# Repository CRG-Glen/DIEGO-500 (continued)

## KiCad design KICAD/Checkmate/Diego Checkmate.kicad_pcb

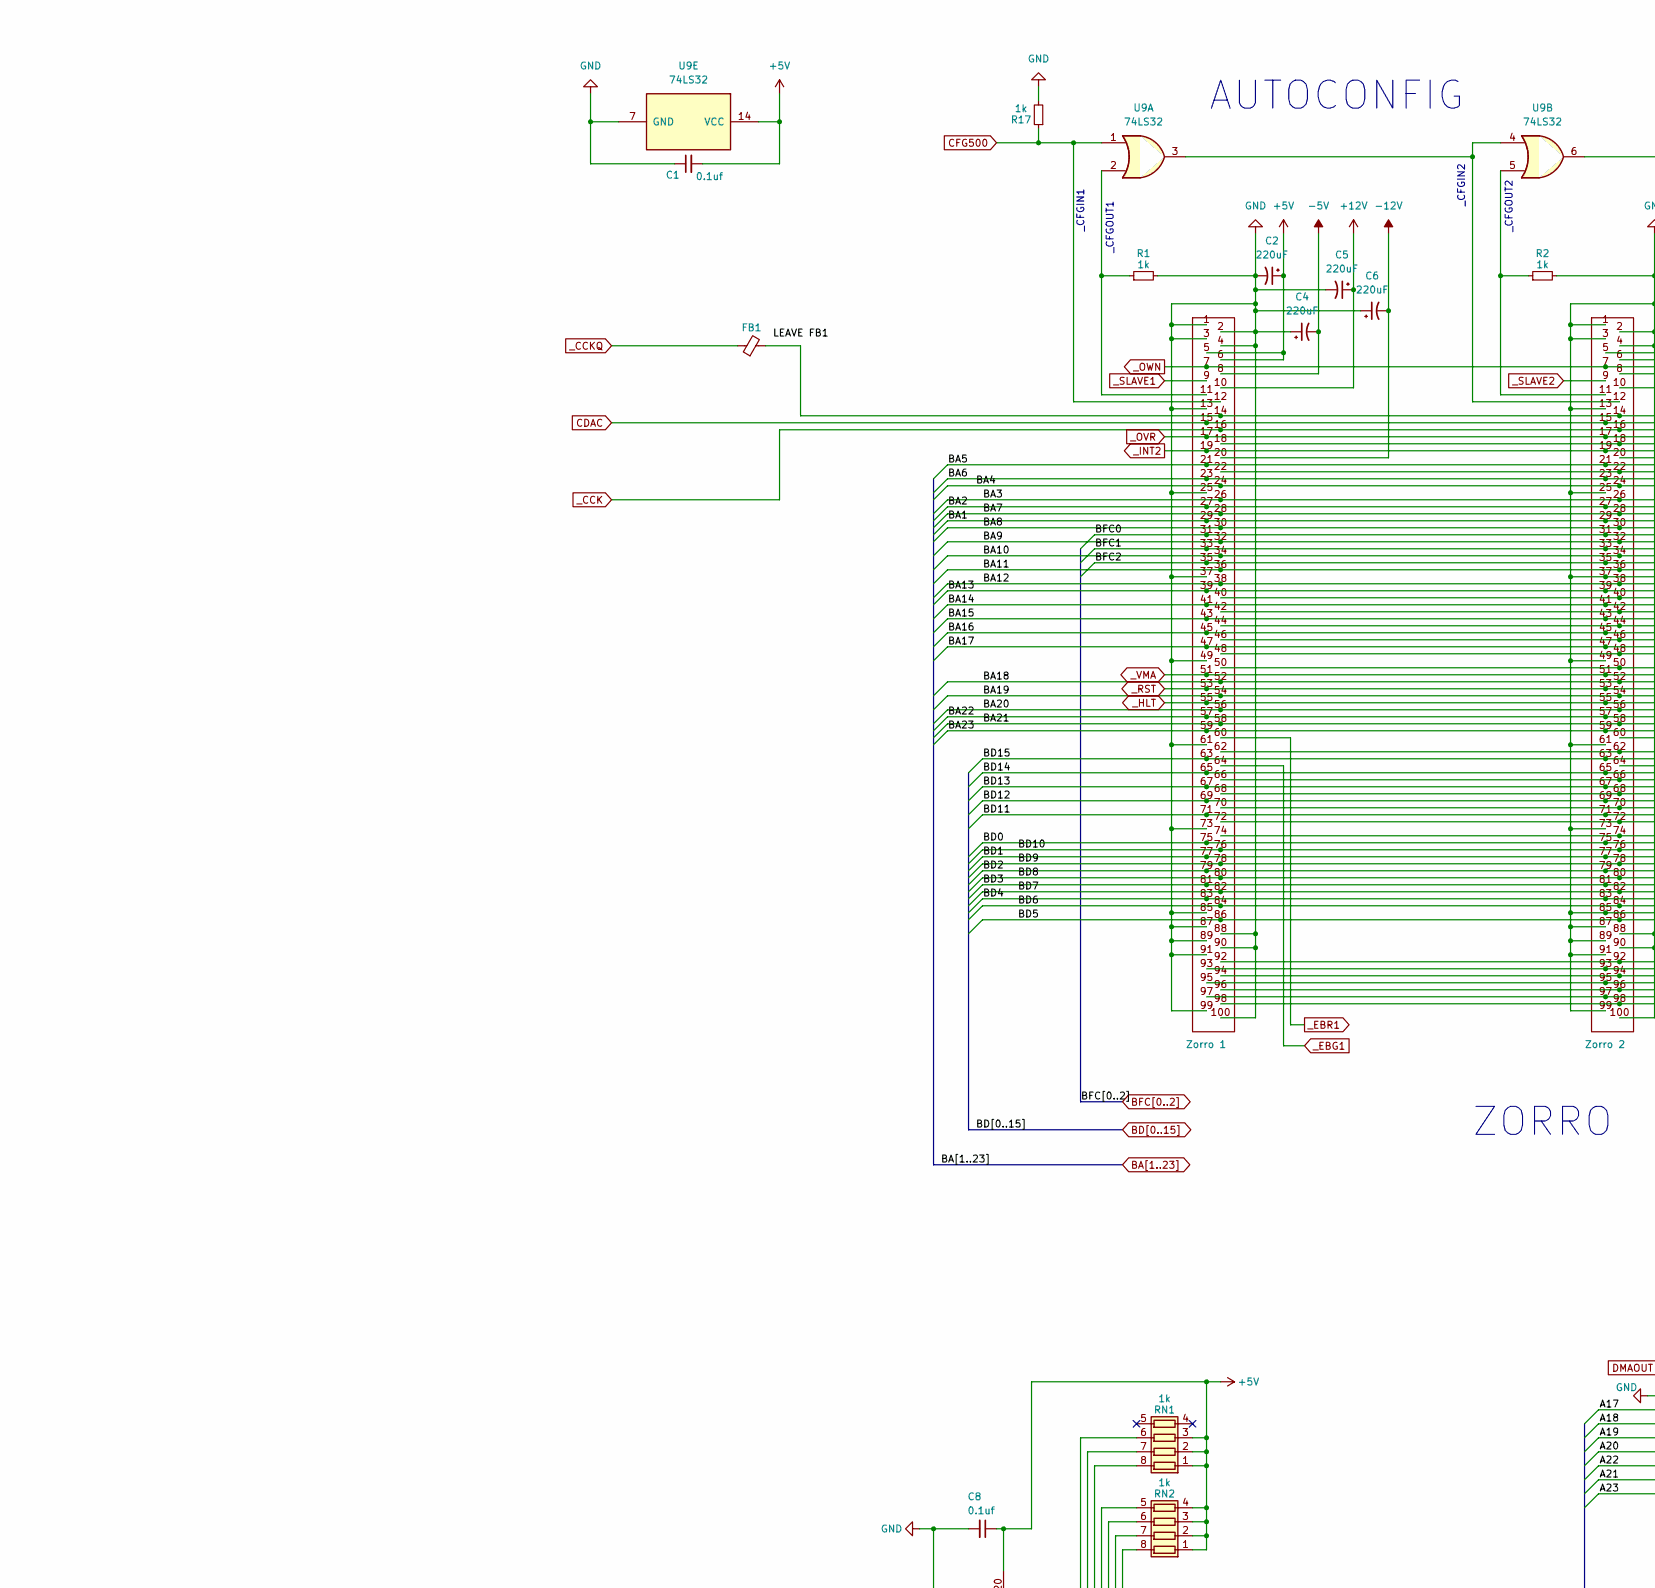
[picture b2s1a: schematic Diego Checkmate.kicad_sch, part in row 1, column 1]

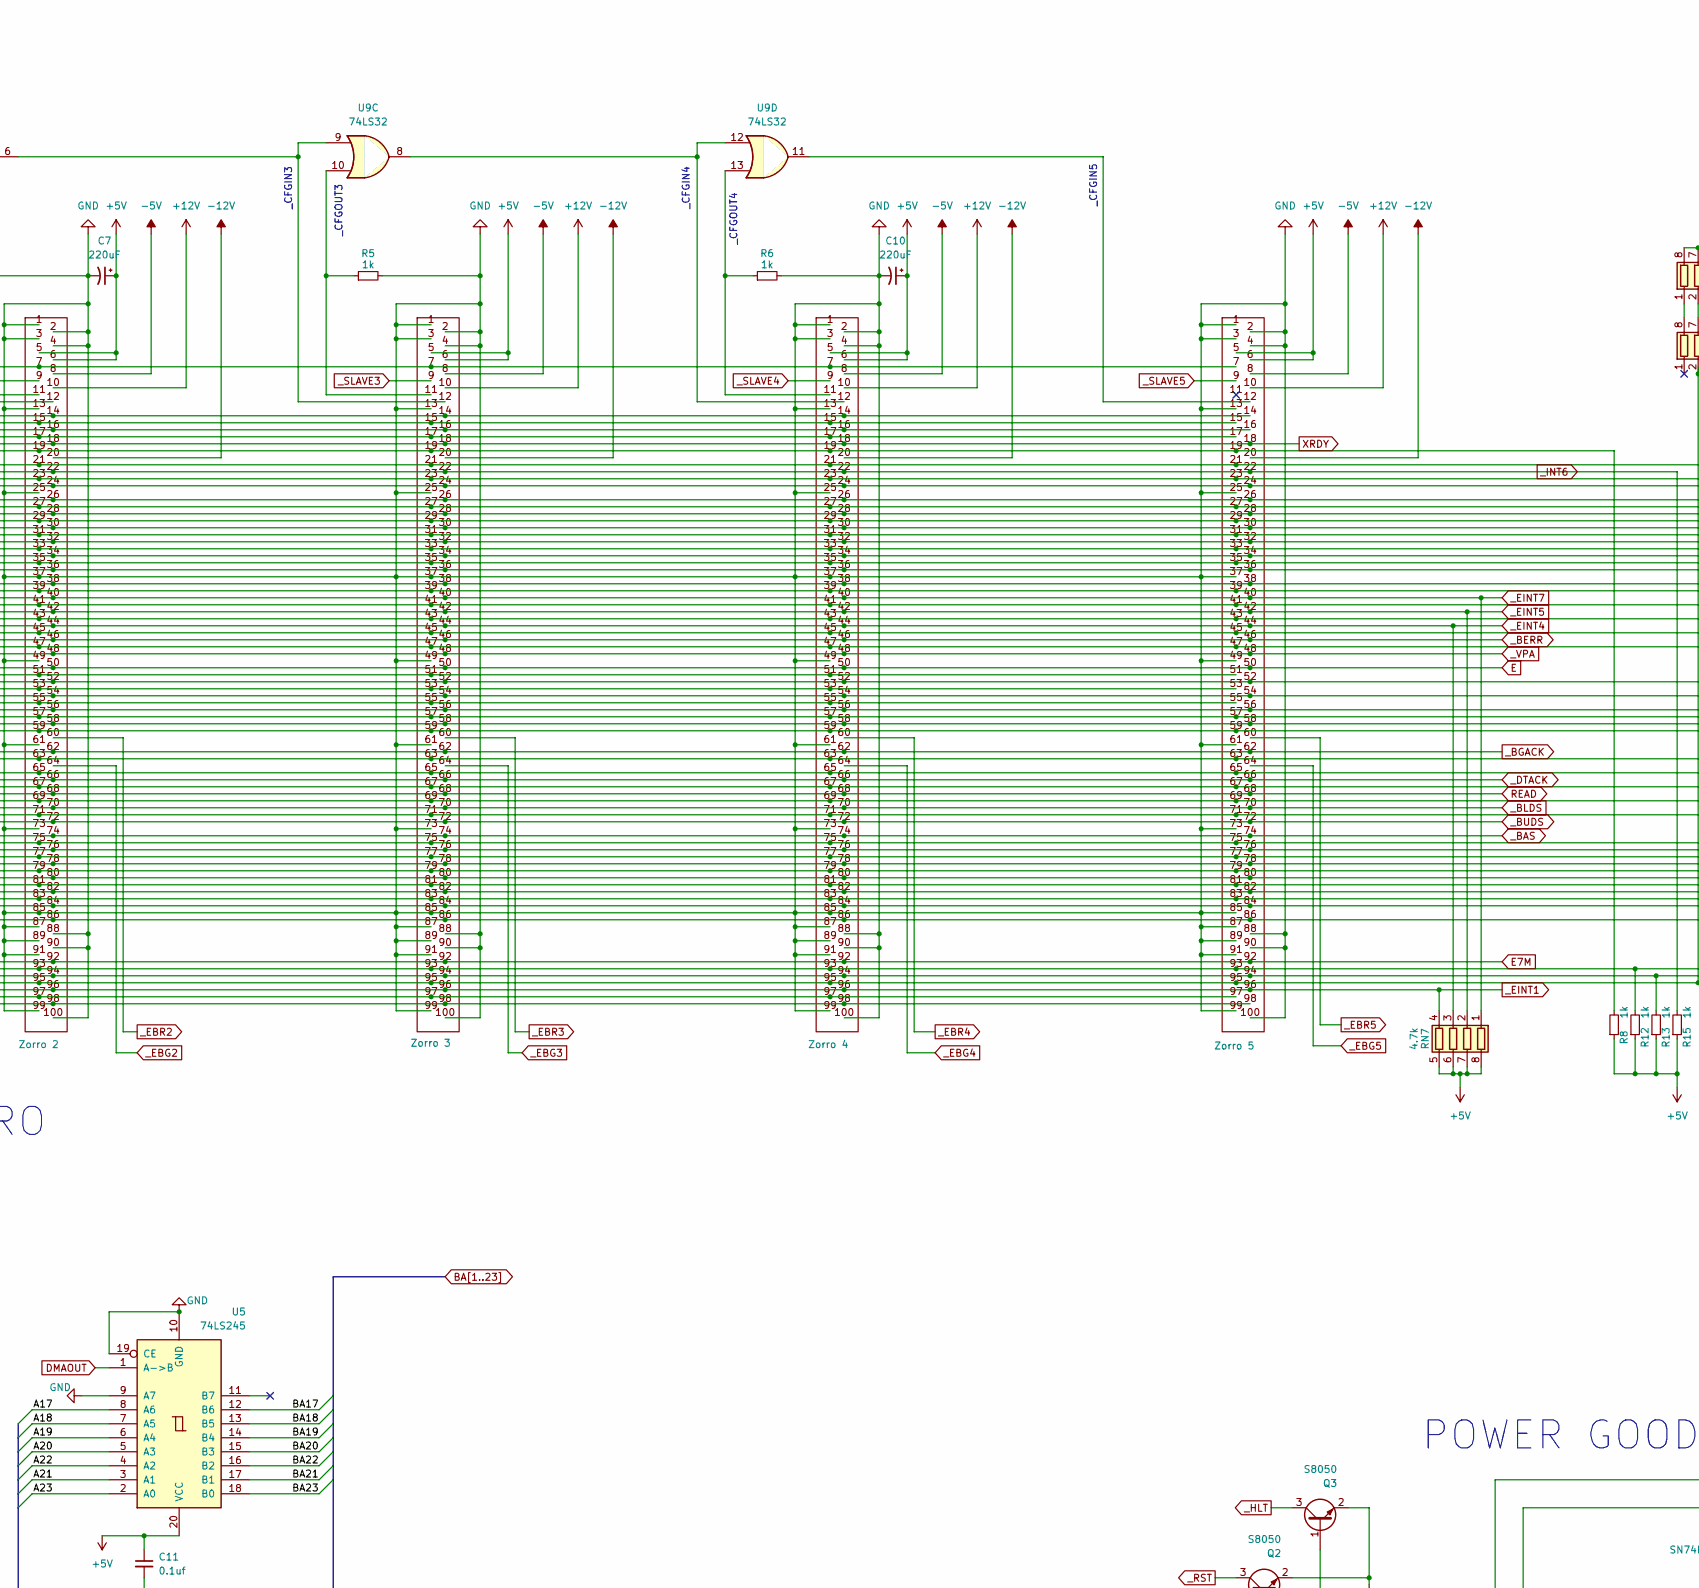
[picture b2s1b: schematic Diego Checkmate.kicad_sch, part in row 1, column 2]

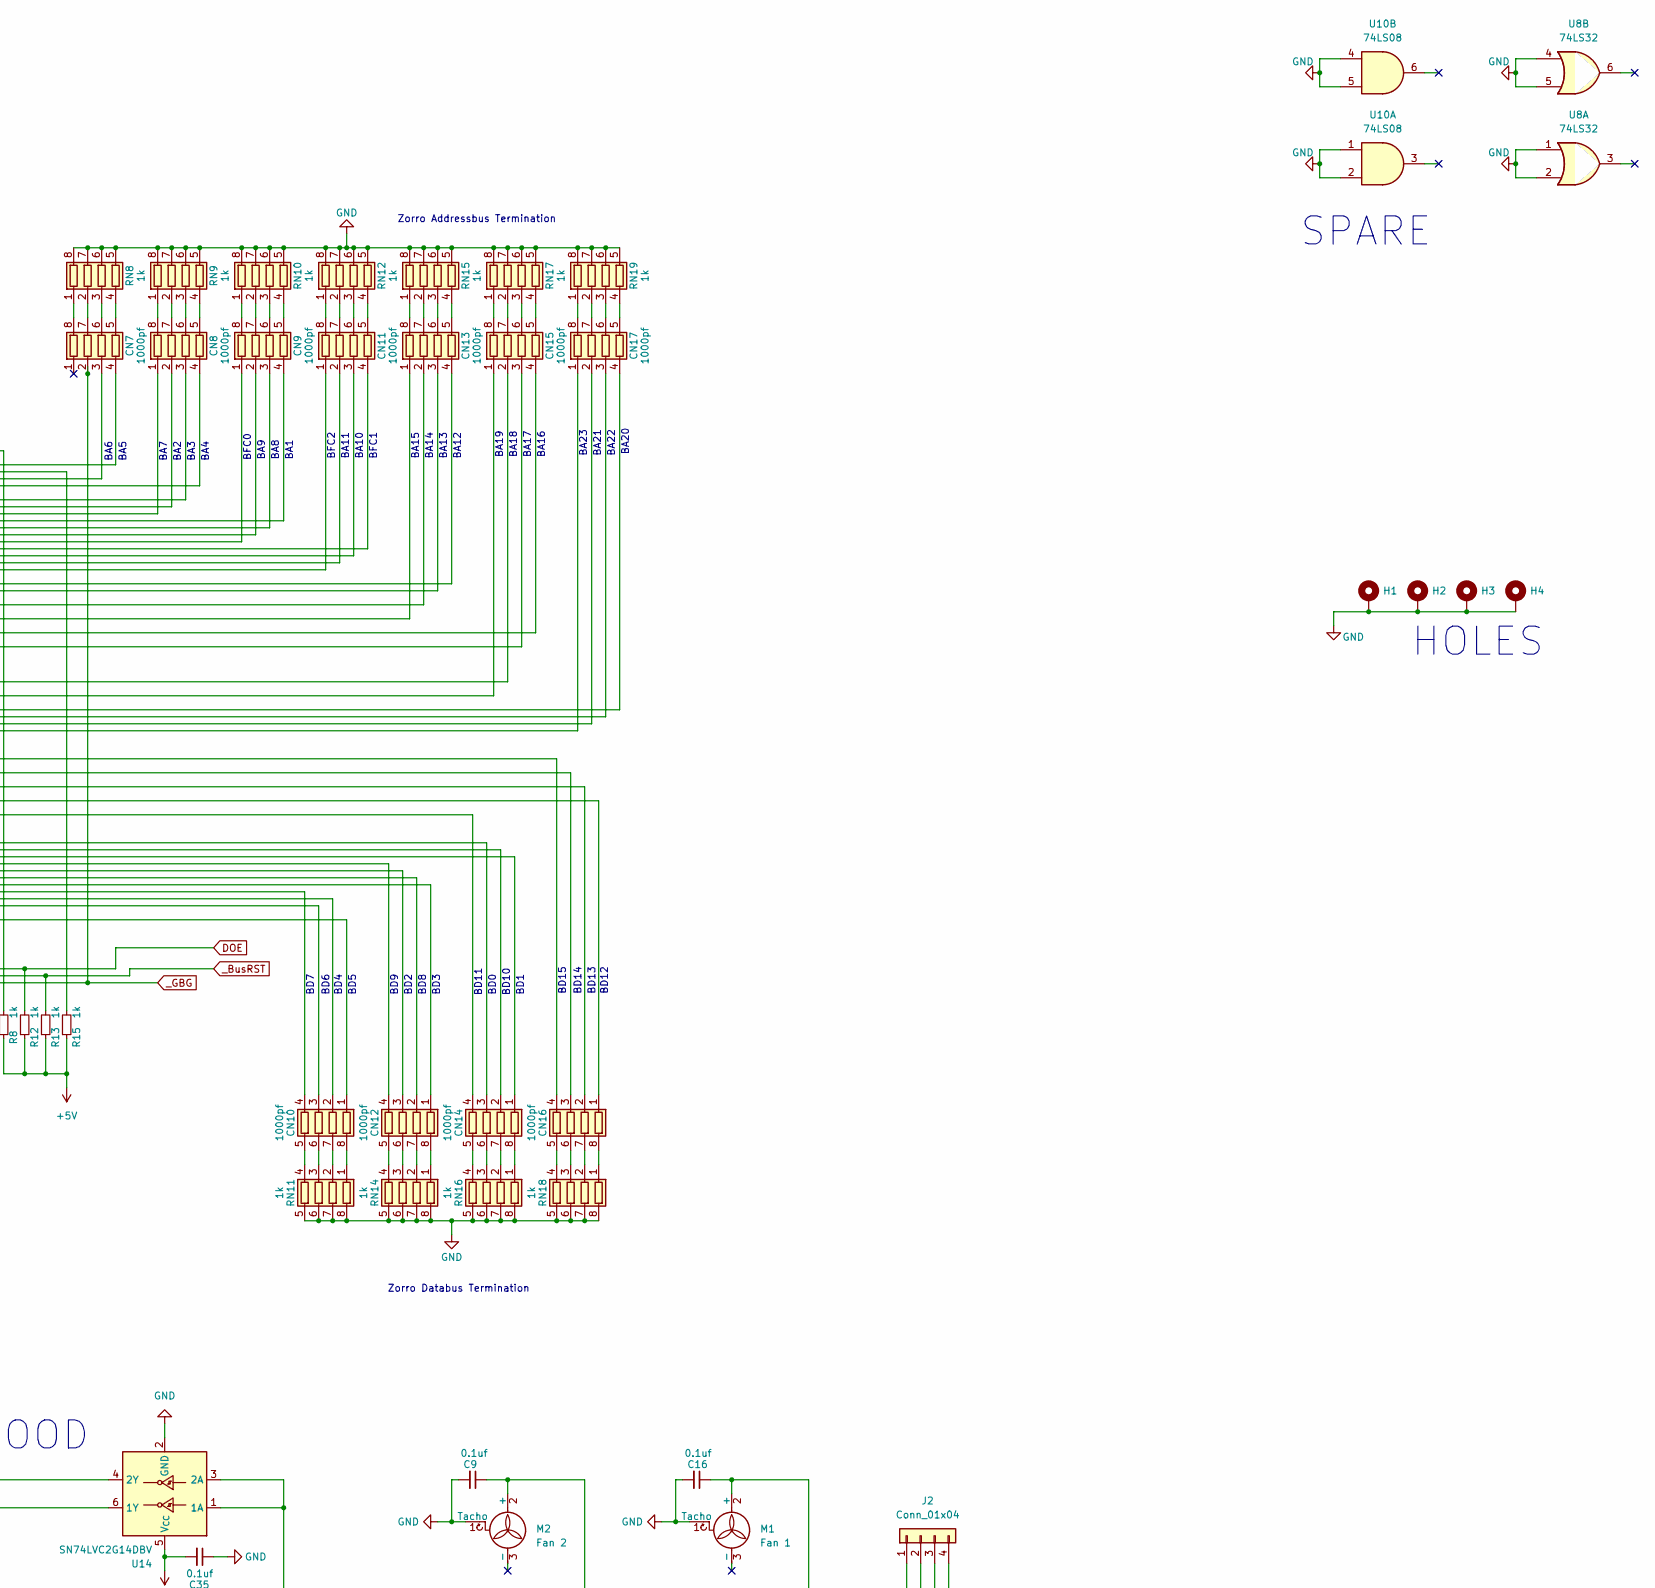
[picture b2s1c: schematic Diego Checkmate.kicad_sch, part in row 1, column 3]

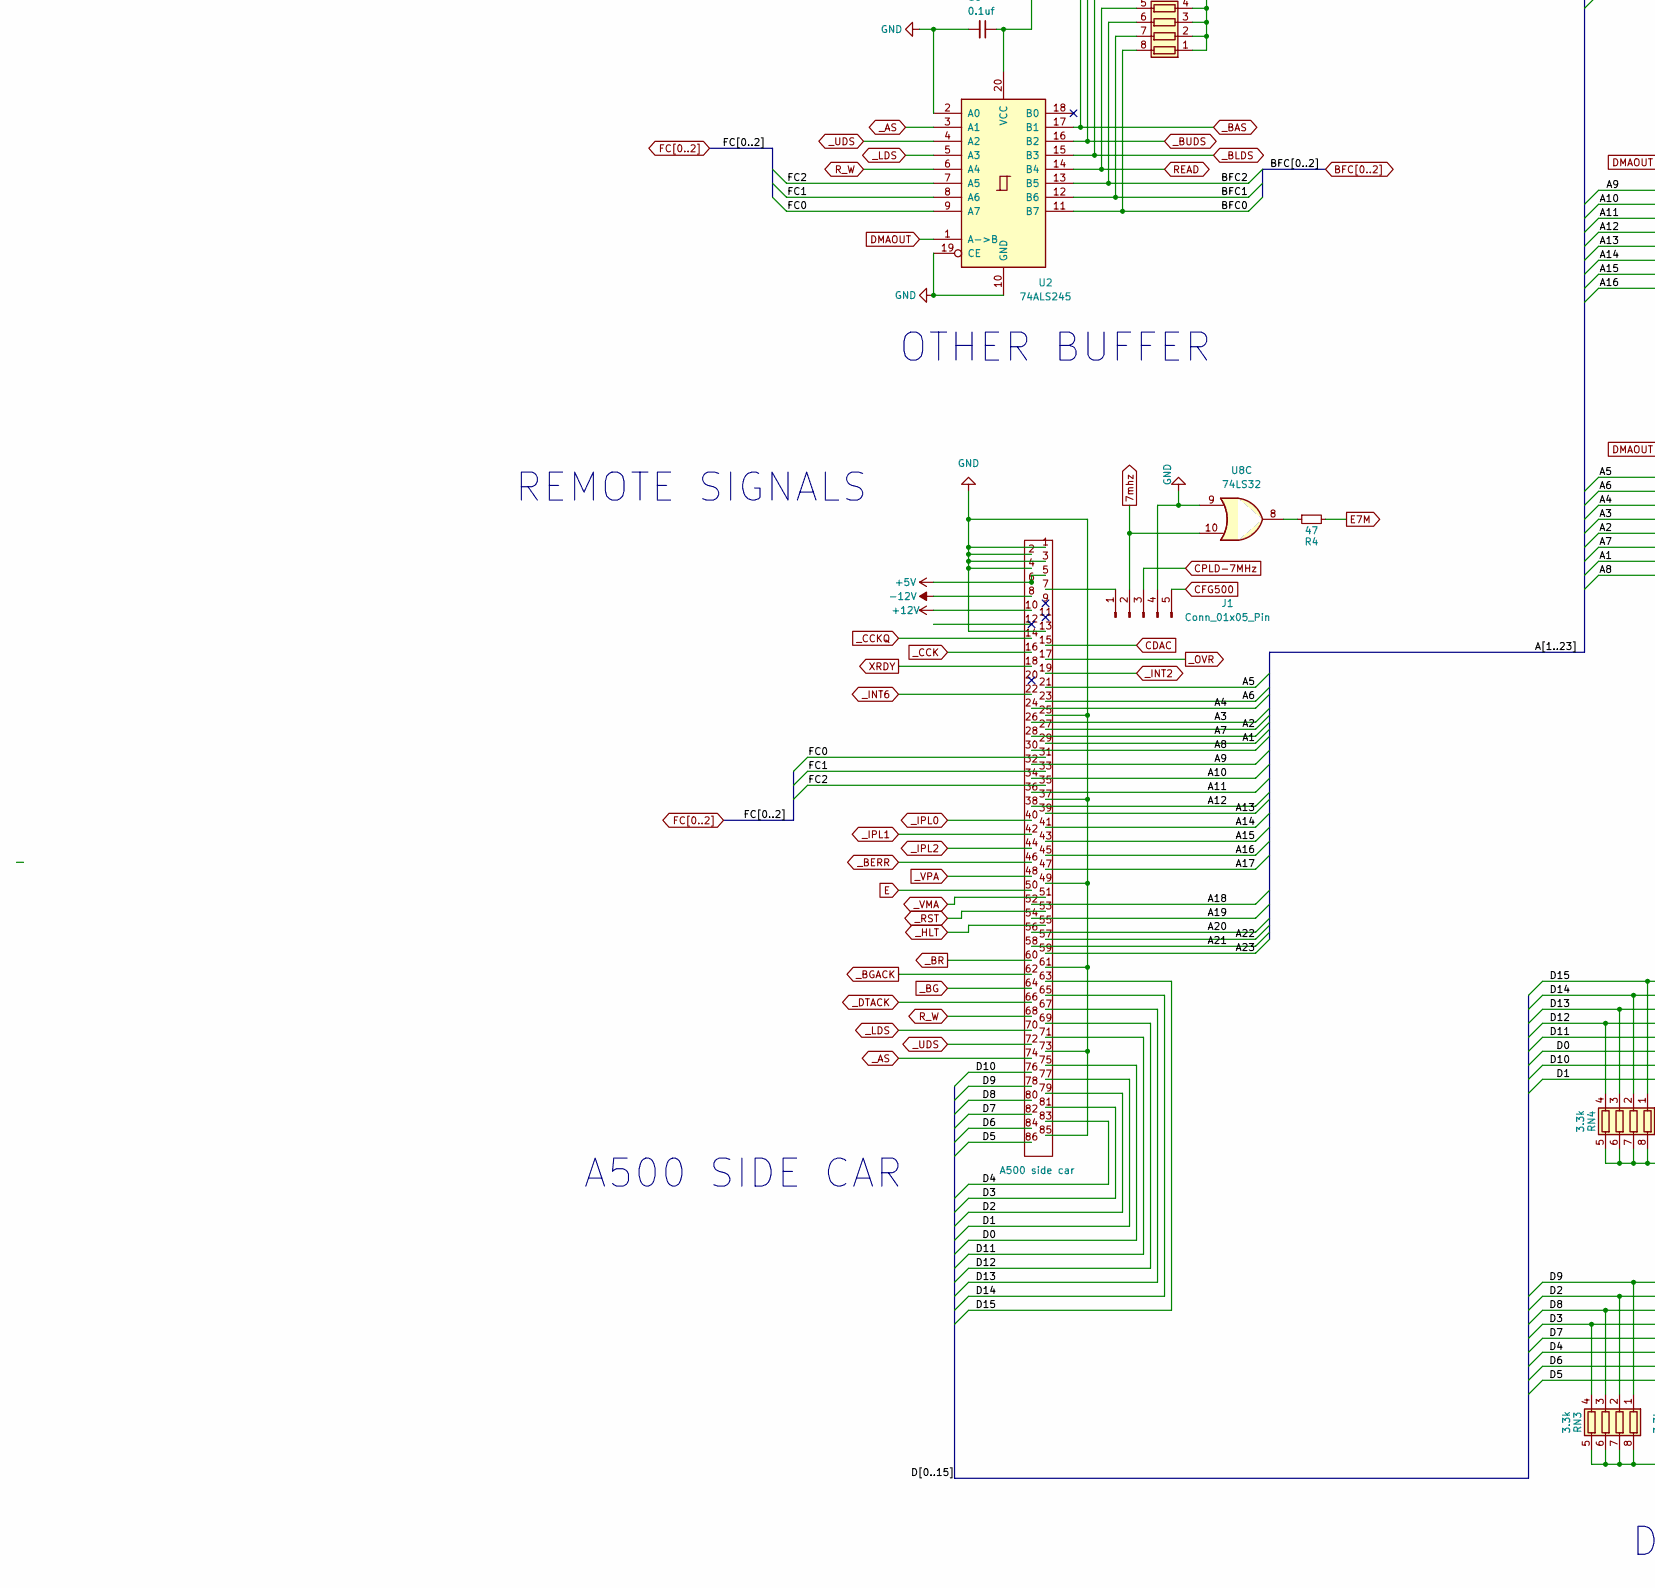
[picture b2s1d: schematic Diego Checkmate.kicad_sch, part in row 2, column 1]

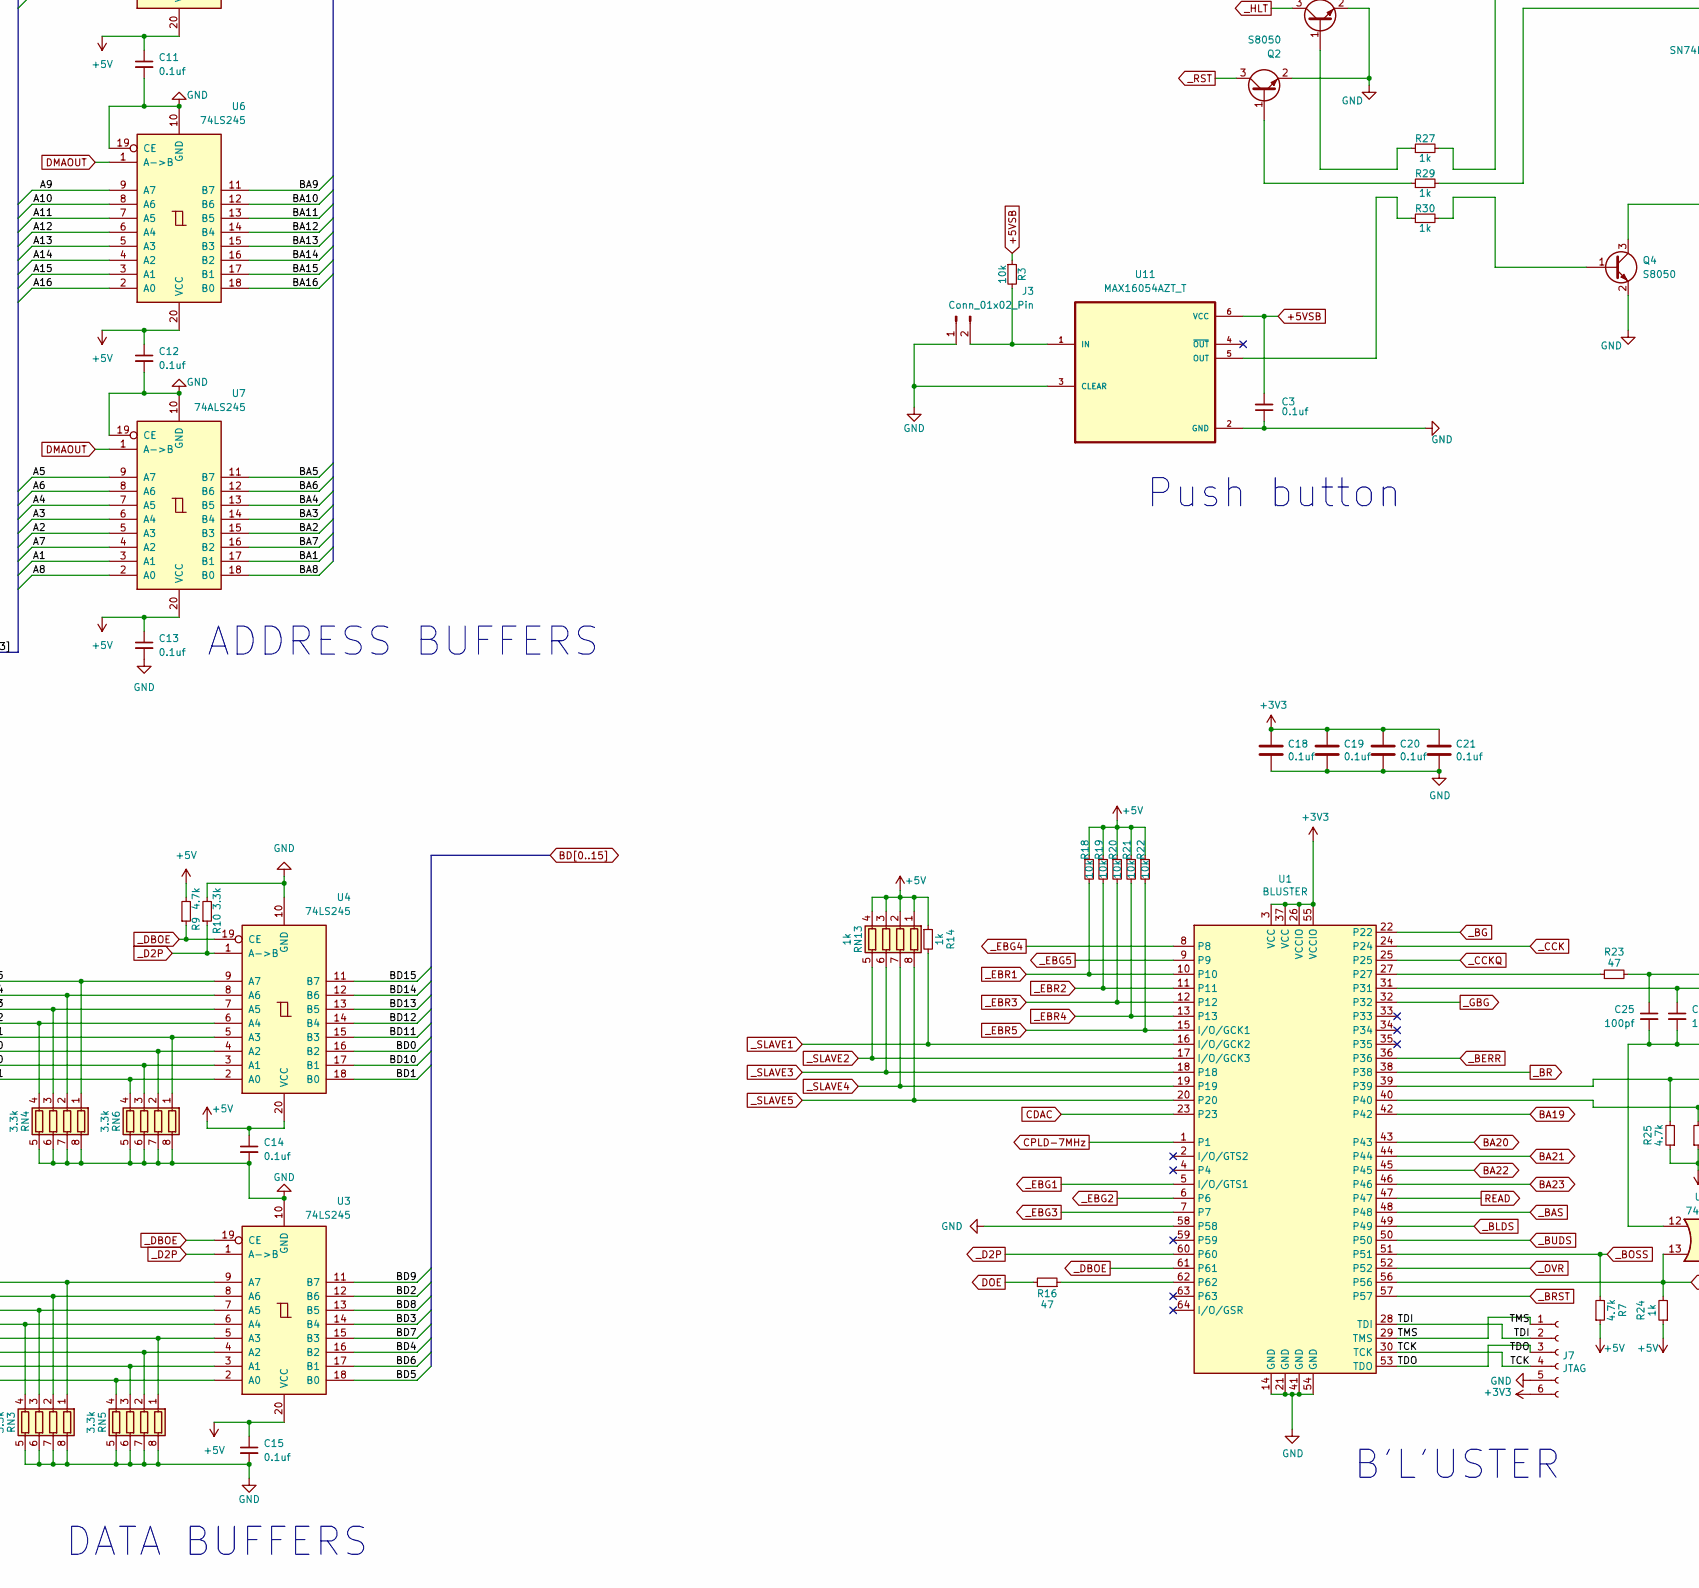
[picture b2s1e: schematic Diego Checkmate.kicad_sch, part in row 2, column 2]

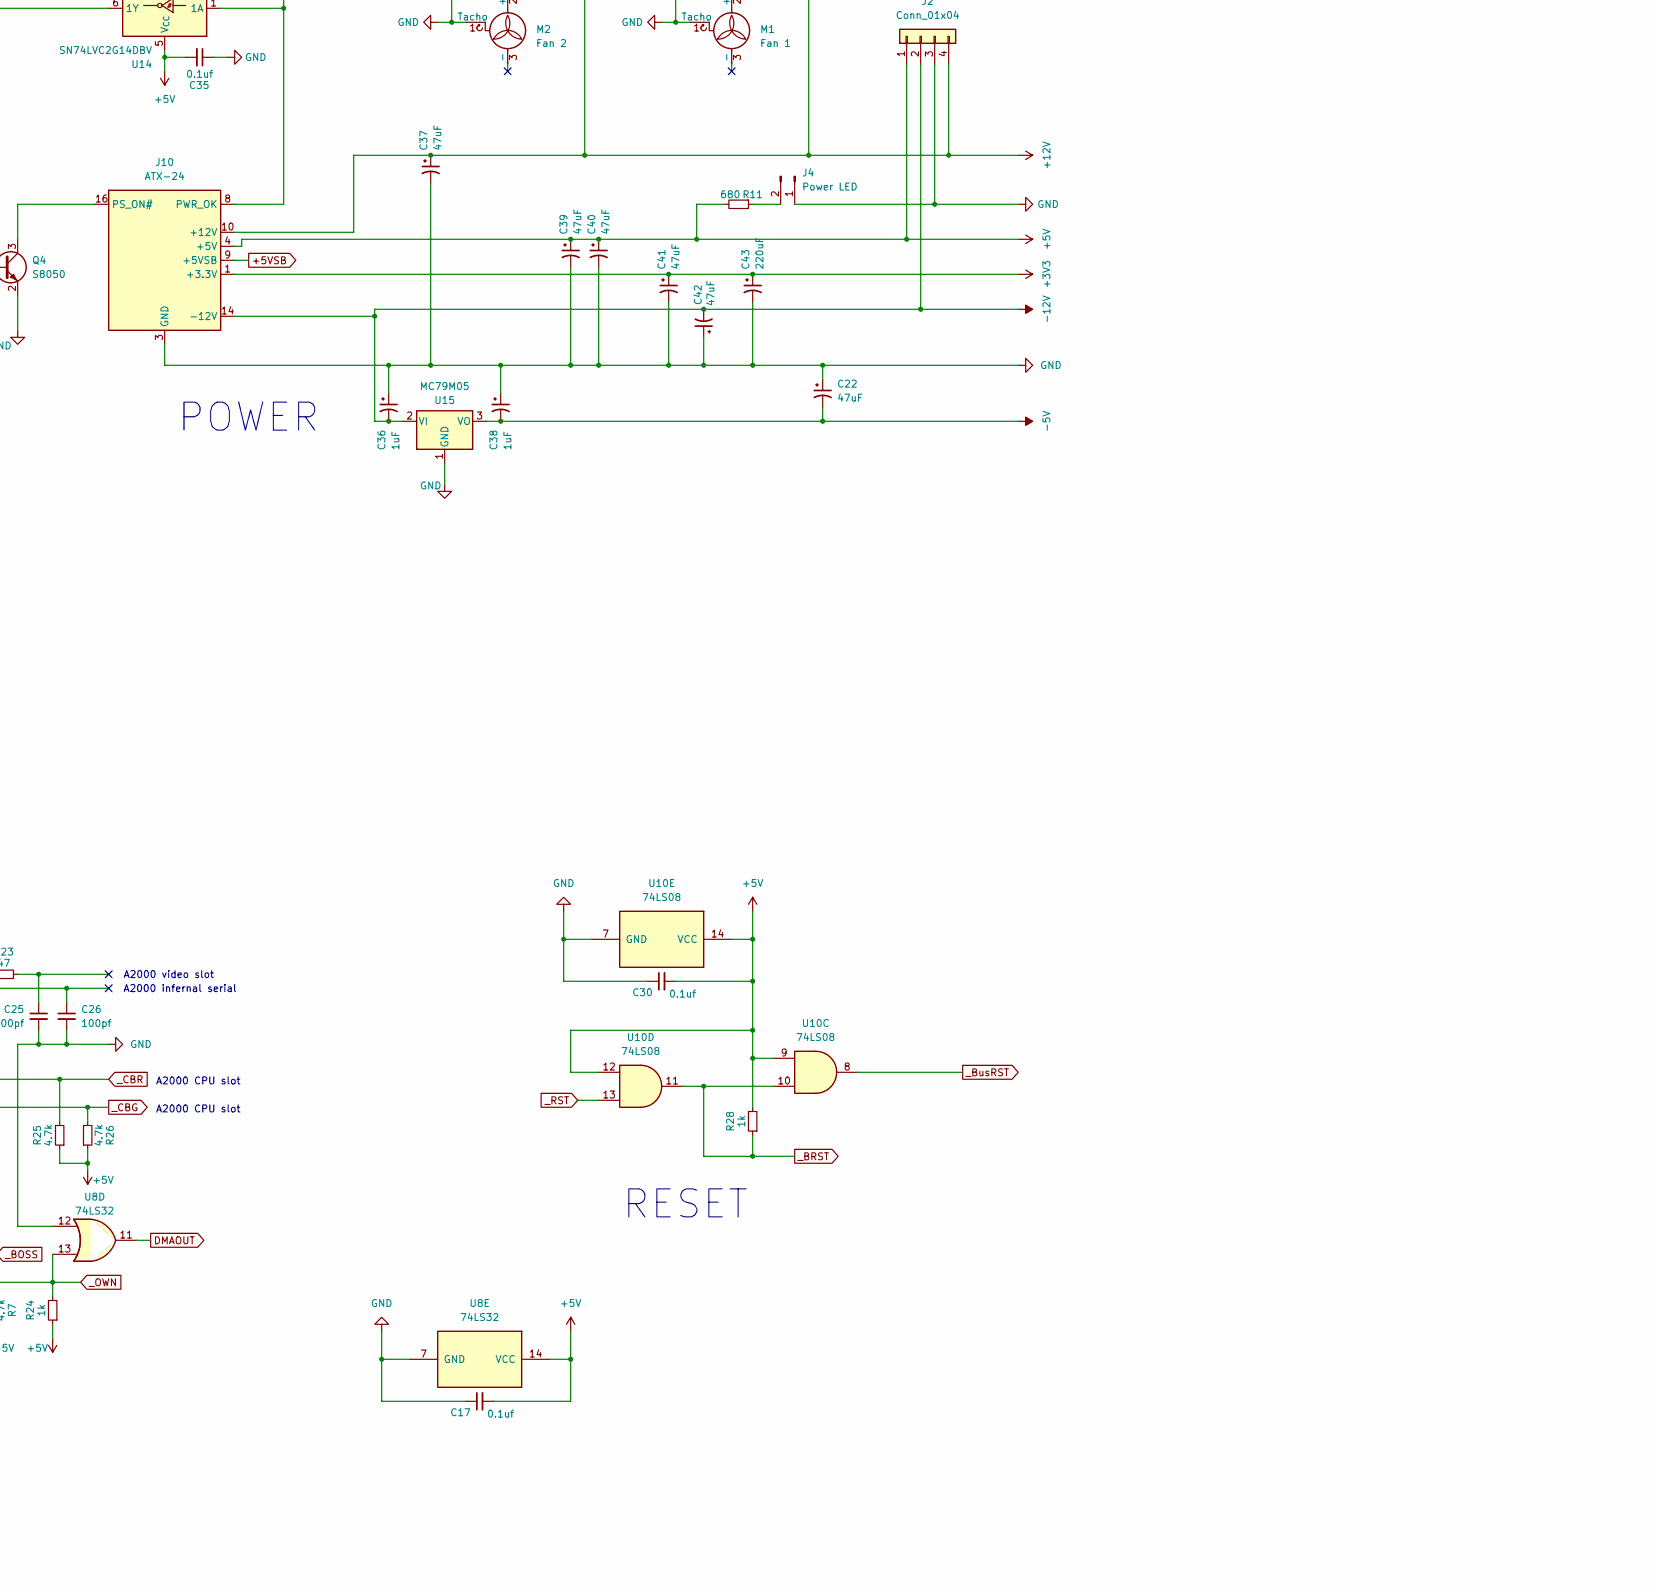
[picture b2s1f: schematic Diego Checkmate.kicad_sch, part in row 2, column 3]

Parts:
C1, C3, C8, C9, C11, C12, C13, C14, C15, C16, C17, C30, C35: 0.1uf; C_0805_2012Metric; LCSC C49678
C2, C4, C5, C6, C7, C10, C43: 220uF; CP_Elec_6.3x7.7; LCSC C278407
C18, C19, C20, C21: 0.1uf; C_0805_2012Metric_Pad1.18x1.45mm_HandSolder; LCSC C49678
C22, C37, C39, C40, C41, C42: 47uF; CP_Elec_6.3x7.7; LCSC C336249
C25, C26: 100pf; C_0805_2012Metric; LCSC C1790
C36, C38: 1uF; CP_Elec_4x5.4; LCSC C3348
CN1: A500 side car; Samtec_HLE-150-02-xx-DV-TE_2x43_P2.54mm_Horizontal; LCSC C5173317
CN2: Zorro 1; Samtec_HLE-150-02-xx-DV-TE_2x50_P2.54mm_Horizontal; LCSC C5173320
CN3: Zorro 2; Samtec_HLE-150-02-xx-DV-TE_2x50_P2.54mm_Horizontal; LCSC C5173320
CN4: Zorro 3; Samtec_HLE-150-02-xx-DV-TE_2x50_P2.54mm_Horizontal; LCSC C5173320
CN5: Zorro 4; Samtec_HLE-150-02-xx-DV-TE_2x50_P2.54mm_Horizontal; LCSC C5173320
CN6: Zorro 5; Samtec_HLE-150-02-xx-DV-TE_2x50_P2.54mm_Horizontal; LCSC C5173320
CN7, CN8, CN9, CN10, CN11, CN12, CN13, CN14, CN15, CN16, CN17: 1000pf; R_Array_Convex_4x0603; LCSC C541606
FB1: FerriteBead_Small; D_0805_2012Metric; LCSC C1015
H1, H2, H3, H4: MountingHole_Pad; MountingHole_4.3mm_M4_DIN965_Pad_TopBottom
J1: Conn_01x05_Pin; PinHeader_1x05_P2.54mm_Vertical
J2: Conn_01x04; Molex_KK-396_5273-04A_1x04_P3.96mm_Vertical
J3: Conn_01x02_Pin; PinHeader_1x02_P2.54mm_Vertical
J4: Power LED; PinHeader_1x02_P2.54mm_Vertical
J7: JTAG; PinHeader_1x06_P2.54mm_Vertical
J10: ATX-24; Molex_Mini-Fit_Jr_5566-24A_2x12_P4.20mm_Vertical
M1: Fan 1; FanPinHeader_1x03_P2.54mm_Vertical
M2: Fan 2; FanPinHeader_1x03_P2.54mm_Vertical
Q2, Q3, Q4: S8050; SOT-23; LCSC C2146
R1, R2, R5, R6, R8, R12, R13, R14, R15, R17, R24, R27, R28, R29, R30: 1k; R_0805_2012Metric; LCSC C17513
R3, R18, R19, R20, R21, R22: 10k; R_0805_2012Metric; LCSC C17414
R4, R16, R23: 47; R_0805_2012Metric; LCSC C17714
R7, R9, R25, R26: 4.7k; R_0805_2012Metric; LCSC C17673
R10: 3.3k; R_0805_2012Metric; LCSC C26010
R11: 680; R_0805_2012Metric; LCSC C17798
RN1, RN2, RN8, RN9, RN10, RN11, RN12, RN13, RN14, RN15, RN16, RN17, RN18, RN19: 1k; R_Array_Convex_4x0603; LCSC C20197
RN3, RN4, RN5, RN6: 3.3k; R_Array_Convex_4x0603; LCSC C425215
RN7: 4.7k; R_Array_Convex_4x0603; LCSC C66697
U1: BLUSTER; TQFP-64_10x10mm_P0.5mm; LCSC C90569
U2, U7: 74ALS245; SO-20_5.3x12.6mm_P1.27mm; LCSC C2675885
U3, U4, U5, U6: 74LS245; SO-20_5.3x12.6mm_P1.27mm; LCSC C7753
U8, U9: 74LS32; SO-14_3.9x8.65mm_P1.27mm; LCSC C116812
U10: 74LS08; SO-14_3.9x8.65mm_P1.27mm; LCSC C6802
U11: MAX16054AZT_T; SOT-23-6; LCSC C79401
U14: SN74LVC2G14DBV; SOT-23-6; LCSC C12401
U15: MC79M05; TO-252-2; LCSC C126401

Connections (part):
7mhz: J1.2, U8.10
+3V3: C18.1, C19.1, C20.1, C21.1, C41.1, C43.1, J7.6, J10.1 (+3.3V), J10.2 (+3.3V), J10.12 (+3.3V), J10.13 (+3.3V), U1.3 (VCC), U1.26 (VCCIO), U1.37 (VCC), U1.55 (VCCIO)
+5V: C1.2, C2.1, C7.1, C8.1, C10.1, C11.1, C12.1, C13.1, C14.1, C15.1, C17.2, C30.2, C35.2, C39.1, C40.1, CN1.5, CN1.6, CN2.5, CN2.6, CN3.5, CN3.6, CN4.5, CN4.6, CN5.5, CN5.6, CN6.5, CN6.6, J2.1, J10.4 (+5V), J10.6 (+5V), J10.21 (+5V), J10.22 (+5V), J10.23 (+5V), R7.1, R8.1, R9.2, R11.2, R12.1, R13.1, R14.1, R15.1, R18.1, R19.1, R20.1, R21.1, R22.1, R24.1, R25.1, R26.1, R28.2, RN1.1 (R1.1), RN1.2 (R2.1), RN1.3 (R3.1), RN2.1 (R1.1), RN2.2 (R2.1), RN2.3 (R3.1), RN2.4 (R4.1), RN7.5 (R4.2), RN7.6 (R3.2), RN7.7 (R2.2), RN7.8 (R1.2), RN13.1 (R1.1), RN13.2 (R2.1), RN13.3 (R3.1), RN13.4 (R4.1), U2.20 (VCC), U3.20 (VCC), U4.20 (VCC), U5.20 (VCC), U6.20 (VCC), U7.20 (VCC), U8.14 (VCC), U9.14 (VCC), U10.9, U10.12, U10.14 (VCC), U14.5 (V_{CC})
+5VSB: C3.2, J10.9 (+5VSB), R3.1, U11.6 (VCC)
+12V: C5.1, C9.1, C16.1, C37.1, CN1.10, CN2.10, CN3.10, CN4.10, CN5.10, CN6.10, J2.4, J10.10 (+12V), J10.11 (+12V), M1.2 (+), M2.2 (+)
-5V: C4.2, C22.2, C38.2, CN2.8, CN3.8, CN4.8, CN5.8, CN6.8, U15.3 (VO)
-12V: C6.2, C36.2, C42.2, CN1.8, CN2.20, CN3.20, CN4.20, CN5.20, CN6.20, J2.2, J10.14 (-12V), U15.2 (VI)
/A1: CN1.29, U7.3 (A1)
/A2: CN1.27, U7.5 (A3)
/A3: CN1.26, U7.6 (A4)
/A4: CN1.24, U7.7 (A5)
/A5: CN1.21, U7.9 (A7)
/A6: CN1.23, U7.8 (A6)
/A7: CN1.28, U7.4 (A2)
/A8: CN1.30, U7.2 (A0)
/A9: CN1.32, U6.9 (A7)
/A10: CN1.34, U6.8 (A6)
/A11: CN1.36, U6.7 (A5)
/A12: CN1.38, U6.6 (A4)
/A13: CN1.39, U6.5 (A3)
/A14: CN1.41, U6.4 (A2)
/A15: CN1.43, U6.3 (A1)
/A16: CN1.45, U6.2 (A0)
/A17: CN1.47, U5.8 (A6)
/A18: CN1.52, U5.7 (A5)
/A19: CN1.54, U5.6 (A4)
/A20: CN1.56, U5.5 (A3)
/A21: CN1.58, U5.3 (A1)
/A22: CN1.57, U5.4 (A2)
/A23: CN1.59, U5.2 (A0)
/D0: CN1.75, RN6.2 (R2.1), U4.4 (A2)
/D1: CN1.77, RN6.4 (R4.1), U4.2 (A0)
/D2: CN1.79, RN3.2 (R2.1), U3.8 (A6)
/D3: CN1.81, RN3.4 (R4.1), U3.6 (A4)
/D4: CN1.83, RN5.2 (R2.1), U3.4 (A2)
/D5: CN1.86, RN5.4 (R4.1), U3.2 (A0)
/D6: CN1.84, RN5.3 (R3.1), U3.3 (A1)
/D7: CN1.82, RN5.1 (R1.1), U3.5 (A3)
/D8: CN1.80, RN3.3 (R3.1), U3.7 (A5)
/D9: CN1.78, RN3.1 (R1.1), U3.9 (A7)
/D10: CN1.76, RN6.3 (R3.1), U4.3 (A1)
/D11: CN1.71, RN6.1 (R1.1), U4.5 (A3)
/D12: CN1.69, RN4.4 (R4.1), U4.6 (A4)
/D13: CN1.67, RN4.3 (R3.1), U4.7 (A5)
/D14: CN1.65, RN4.2 (R2.1), U4.8 (A6)
/D15: CN1.63, RN4.1 (R1.1), U4.9 (A7)
/TCK: J7.4, U1.30 (TCK)
/TDI: J7.2, U1.28 (TDI)
/TDO: J7.3, U1.53 (TDO)
/TMS: J7.1, U1.29 (TMS)
BA1: CN2.29, CN3.29, CN4.29, CN5.29, CN6.29, CN9.4 (R4.1), U7.17 (B1)
BA2: CN2.27, CN3.27, CN4.27, CN5.27, CN6.27, CN8.2 (R2.1), U7.15 (B3)
BA3: CN2.26, CN3.26, CN4.26, CN5.26, CN6.26, CN8.3 (R3.1), U7.14 (B4)
BA4: CN2.24, CN3.24, CN4.24, CN5.24, CN6.24, CN8.4 (R4.1), U7.13 (B5)
BA5: CN2.21, CN3.21, CN4.21, CN5.21, CN6.21, CN7.4 (R4.1), U7.11 (B7)
BA6: CN2.23, CN3.23, CN4.23, CN5.23, CN6.23, CN7.3 (R3.1), U7.12 (B6)
BA7: CN2.28, CN3.28, CN4.28, CN5.28, CN6.28, CN8.1 (R1.1), U7.16 (B2)
BA8: CN2.30, CN3.30, CN4.30, CN5.30, CN6.30, CN9.3 (R3.1), U7.18 (B0)
BA9: CN2.32, CN3.32, CN4.32, CN5.32, CN6.32, CN9.1 (R1.1), U6.11 (B7)
BA10: CN2.34, CN3.34, CN4.34, CN5.34, CN6.34, CN11.3 (R3.1), U6.12 (B6)
BA11: CN2.36, CN3.36, CN4.36, CN5.36, CN6.36, CN11.1 (R1.1), U6.13 (B5)
BA12: CN2.38, CN3.38, CN4.38, CN5.38, CN6.38, CN13.4 (R4.1), U6.14 (B4)
BA13: CN2.39, CN3.39, CN4.39, CN5.39, CN6.39, CN13.3 (R3.1), U6.15 (B3)
BA14: CN2.41, CN3.41, CN4.41, CN5.41, CN6.41, CN13.2 (R2.1), U6.16 (B2)
BA15: CN2.43, CN3.43, CN4.43, CN5.43, CN6.43, CN13.1 (R1.1), U6.17 (B1)
BA16: CN2.45, CN3.45, CN4.45, CN5.45, CN6.45, CN15.4 (R4.1), U6.18 (B0)
BA17: CN2.47, CN3.47, CN4.47, CN5.47, CN6.47, CN15.3 (R3.1), U5.12 (B6)
BA18: CN2.52, CN3.52, CN4.52, CN5.52, CN6.52, CN15.2 (R2.1), U5.13 (B5)
BA19: CN2.54, CN3.54, CN4.54, CN5.54, CN6.54, CN15.1 (R1.1), U1.42, U5.14 (B4)
BA20: CN2.56, CN3.56, CN4.56, CN5.56, CN6.56, CN17.4 (R4.1), U1.43, U5.15 (B3)
BA21: CN2.58, CN3.58, CN4.58, CN5.58, CN6.58, CN17.2 (R2.1), U1.44, U5.17 (B1)
BA22: CN2.57, CN3.57, CN4.57, CN5.57, CN6.57, CN17.3 (R3.1), U1.45, U5.16 (B2)
BA23: CN2.59, CN3.59, CN4.59, CN5.59, CN6.59, CN17.1 (R1.1), U1.46, U5.18 (B0)
BD0: CN2.75, CN3.75, CN4.75, CN5.75, CN6.75, CN14.3 (R3.1), U4.16 (B2)
BD1: CN2.77, CN3.77, CN4.77, CN5.77, CN6.77, CN14.1 (R1.1), U4.18 (B0)
BD2: CN2.79, CN3.79, CN4.79, CN5.79, CN6.79, CN12.3 (R3.1), U3.12 (B6)
BD3: CN2.81, CN3.81, CN4.81, CN5.81, CN6.81, CN12.1 (R1.1), U3.14 (B4)
BD4: CN2.83, CN3.83, CN4.83, CN5.83, CN6.83, CN10.2 (R2.1), U3.16 (B2)
BD5: CN2.86, CN3.86, CN4.86, CN5.86, CN6.86, CN10.1 (R1.1), U3.18 (B0)
BD6: CN2.84, CN3.84, CN4.84, CN5.84, CN6.84, CN10.3 (R3.1), U3.17 (B1)
BD7: CN2.82, CN3.82, CN4.82, CN5.82, CN6.82, CN10.4 (R4.1), U3.15 (B3)
BD8: CN2.80, CN3.80, CN4.80, CN5.80, CN6.80, CN12.2 (R2.1), U3.13 (B5)
BD9: CN2.78, CN3.78, CN4.78, CN5.78, CN6.78, CN12.4 (R4.1), U3.11 (B7)
BD10: CN2.76, CN3.76, CN4.76, CN5.76, CN6.76, CN14.2 (R2.1), U4.17 (B1)
BD11: CN2.71, CN3.71, CN4.71, CN5.71, CN6.71, CN14.4 (R4.1), U4.15 (B3)
BD12: CN2.69, CN3.69, CN4.69, CN5.69, CN6.69, CN16.1 (R1.1), U4.14 (B4)
BD13: CN2.67, CN3.67, CN4.67, CN5.67, CN6.67, CN16.2 (R2.1), U4.13 (B5)
BD14: CN2.65, CN3.65, CN4.65, CN5.65, CN6.65, CN16.3 (R3.1), U4.12 (B6)
BD15: CN2.63, CN3.63, CN4.63, CN5.63, CN6.63, CN16.4 (R4.1), U4.11 (B7)
BFC0: CN2.31, CN3.31, CN4.31, CN5.31, CN6.31, CN9.2 (R2.1), RN2.8 (R1.2), U2.11 (B7)
BFC1: CN2.33, CN3.33, CN4.33, CN5.33, CN6.33, CN11.4 (R4.1), RN2.7 (R2.2), U2.12 (B6)
BFC2: CN2.35, CN3.35, CN4.35, CN5.35, CN6.35, CN11.2 (R2.1), RN2.6 (R3.2), U2.13 (B5)
CDAC: CN1.15, CN2.15, CN3.15, CN4.15, CN5.15, CN6.15, U1.23
CFG500: CN2.12, J1.5, R17.1, U9.1
CPLD-7MHz: J1.3, U1.1
DMAOUT: U2.1 (A->B), U5.1 (A->B), U6.1 (A->B), U7.1 (A->B), U8.11
DOE: CN2.93, CN3.93, CN4.93, CN5.93, CN6.93, R12.2, R16.2
E: CN1.50, CN2.50, CN3.50, CN4.50, CN5.50, CN6.50
E7M: CN2.92, CN3.92, CN4.92, CN5.92, CN6.92, R4.2
FC0: CN1.31, U2.9 (A7)
FC1: CN1.33, U2.8 (A6)
FC2: CN1.35, U2.7 (A5)
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
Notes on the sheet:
BD7
BA15
_CFGOUT2
BA21
BA8
BD6
BD12
BFC1
BA16
BA13
BD1
_CFGIN4
AUTOCONFIG
_CFGIN5
BD10
BA18
_CFGIN1
BA5
OTHER BUFFER
SPARE
BA3
BA17
REMOTE SIGNALS
POWER GOOD
Push button
BA9
BA1
BD4
BA7
ZORRO
A2000 video slot
BFC0
BFC2
BA6
RESET
BA22
_CFGOUT3
_CFGIN2
BA23
BD0

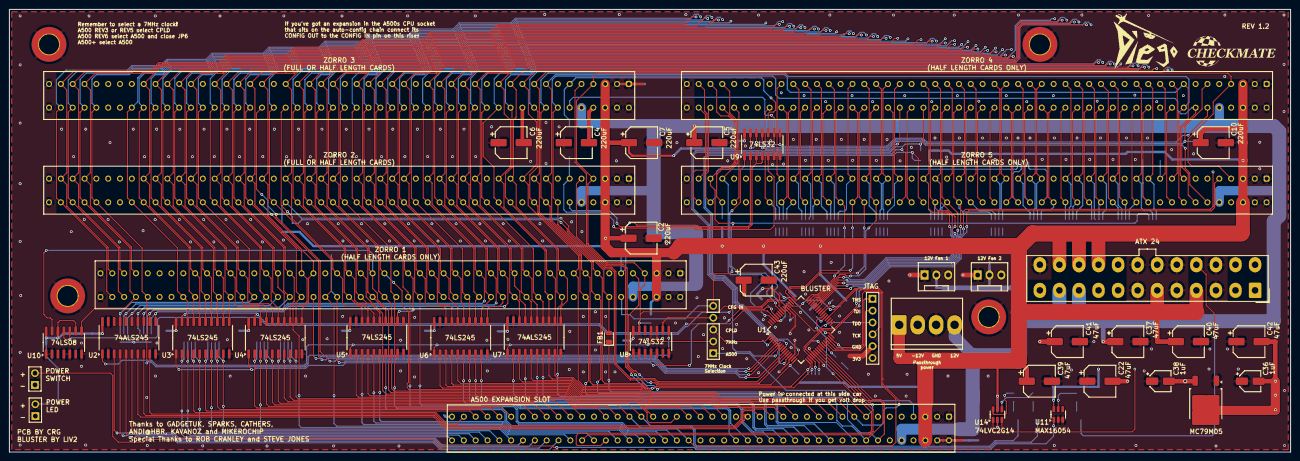
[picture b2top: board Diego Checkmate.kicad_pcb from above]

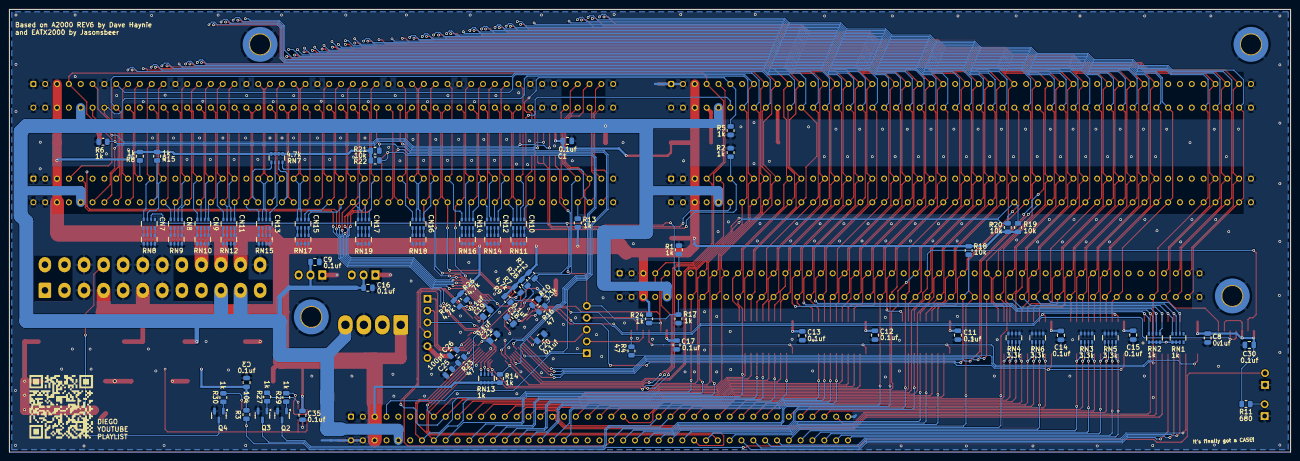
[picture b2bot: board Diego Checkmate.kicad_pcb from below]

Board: 4 copper layers, 275.0 x 95.0 mm, 129 parts (82 on the bottom side), 223 nets.

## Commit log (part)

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2026-02-25 Revise README for DIEGO 500 project
    Updated README to improve clarity and add information about the DIEGO 500 project.
2026-02-25 Revise README for DIEGO 500 project
    Updated README to include new project details and structure.
2026-02-27 3 slot added
2026-02-27 General update
2026-03-06 Fix autoconfig error
2026-03-06 Revise README for DIEGO 500 project
    Updated README to reflect project details and licensing.
2026-03-06 Revise README for DIEGO 500 project
    Updated README.md to improve formatting and clarity.
2026-03-06 License updated
    Updated the license from CERN Open Hardware License to Creative Commons Attribution-NonCommercial-ShareAlike 4.0 International Public License.
2026-03-06 Revise README for DIEGO 500
    Updated README to include project details and assembly instructions.
2026-03-06 License updated
    Updated the license from Creative Commons Attribution-NonCommercial-ShareAlike 4.0 to CERN Open Hardware Licence, including definitions and conditions for use, modification, and distribution.
2026-04-16 Update README with project details and FAQs
2026-04-21 KICAD and JLC files updated
2026-04-23 Revise CERN Open Hardware Licence text
    Updated the CERN Open Hardware Licence to reflect the correct variant and made various clarifications throughout the text.
2026-04-23 Revise LICENSE.md
    Updated definitions and clauses in the CERN-OHL-S License.
2026-04-23 Revise README for DIEGO 500 version 1.1
    Updated README to reflect version 1.1 changes, including ordering details, assembly instructions, and additional FAQs.
2026-04-27 Base 3D files added
2026-04-27 Revise README for DIEGO 500 project
    Updated README to include additional details about the DIEGO 500 project, including assembly instructions, testing results, and licensing information.
